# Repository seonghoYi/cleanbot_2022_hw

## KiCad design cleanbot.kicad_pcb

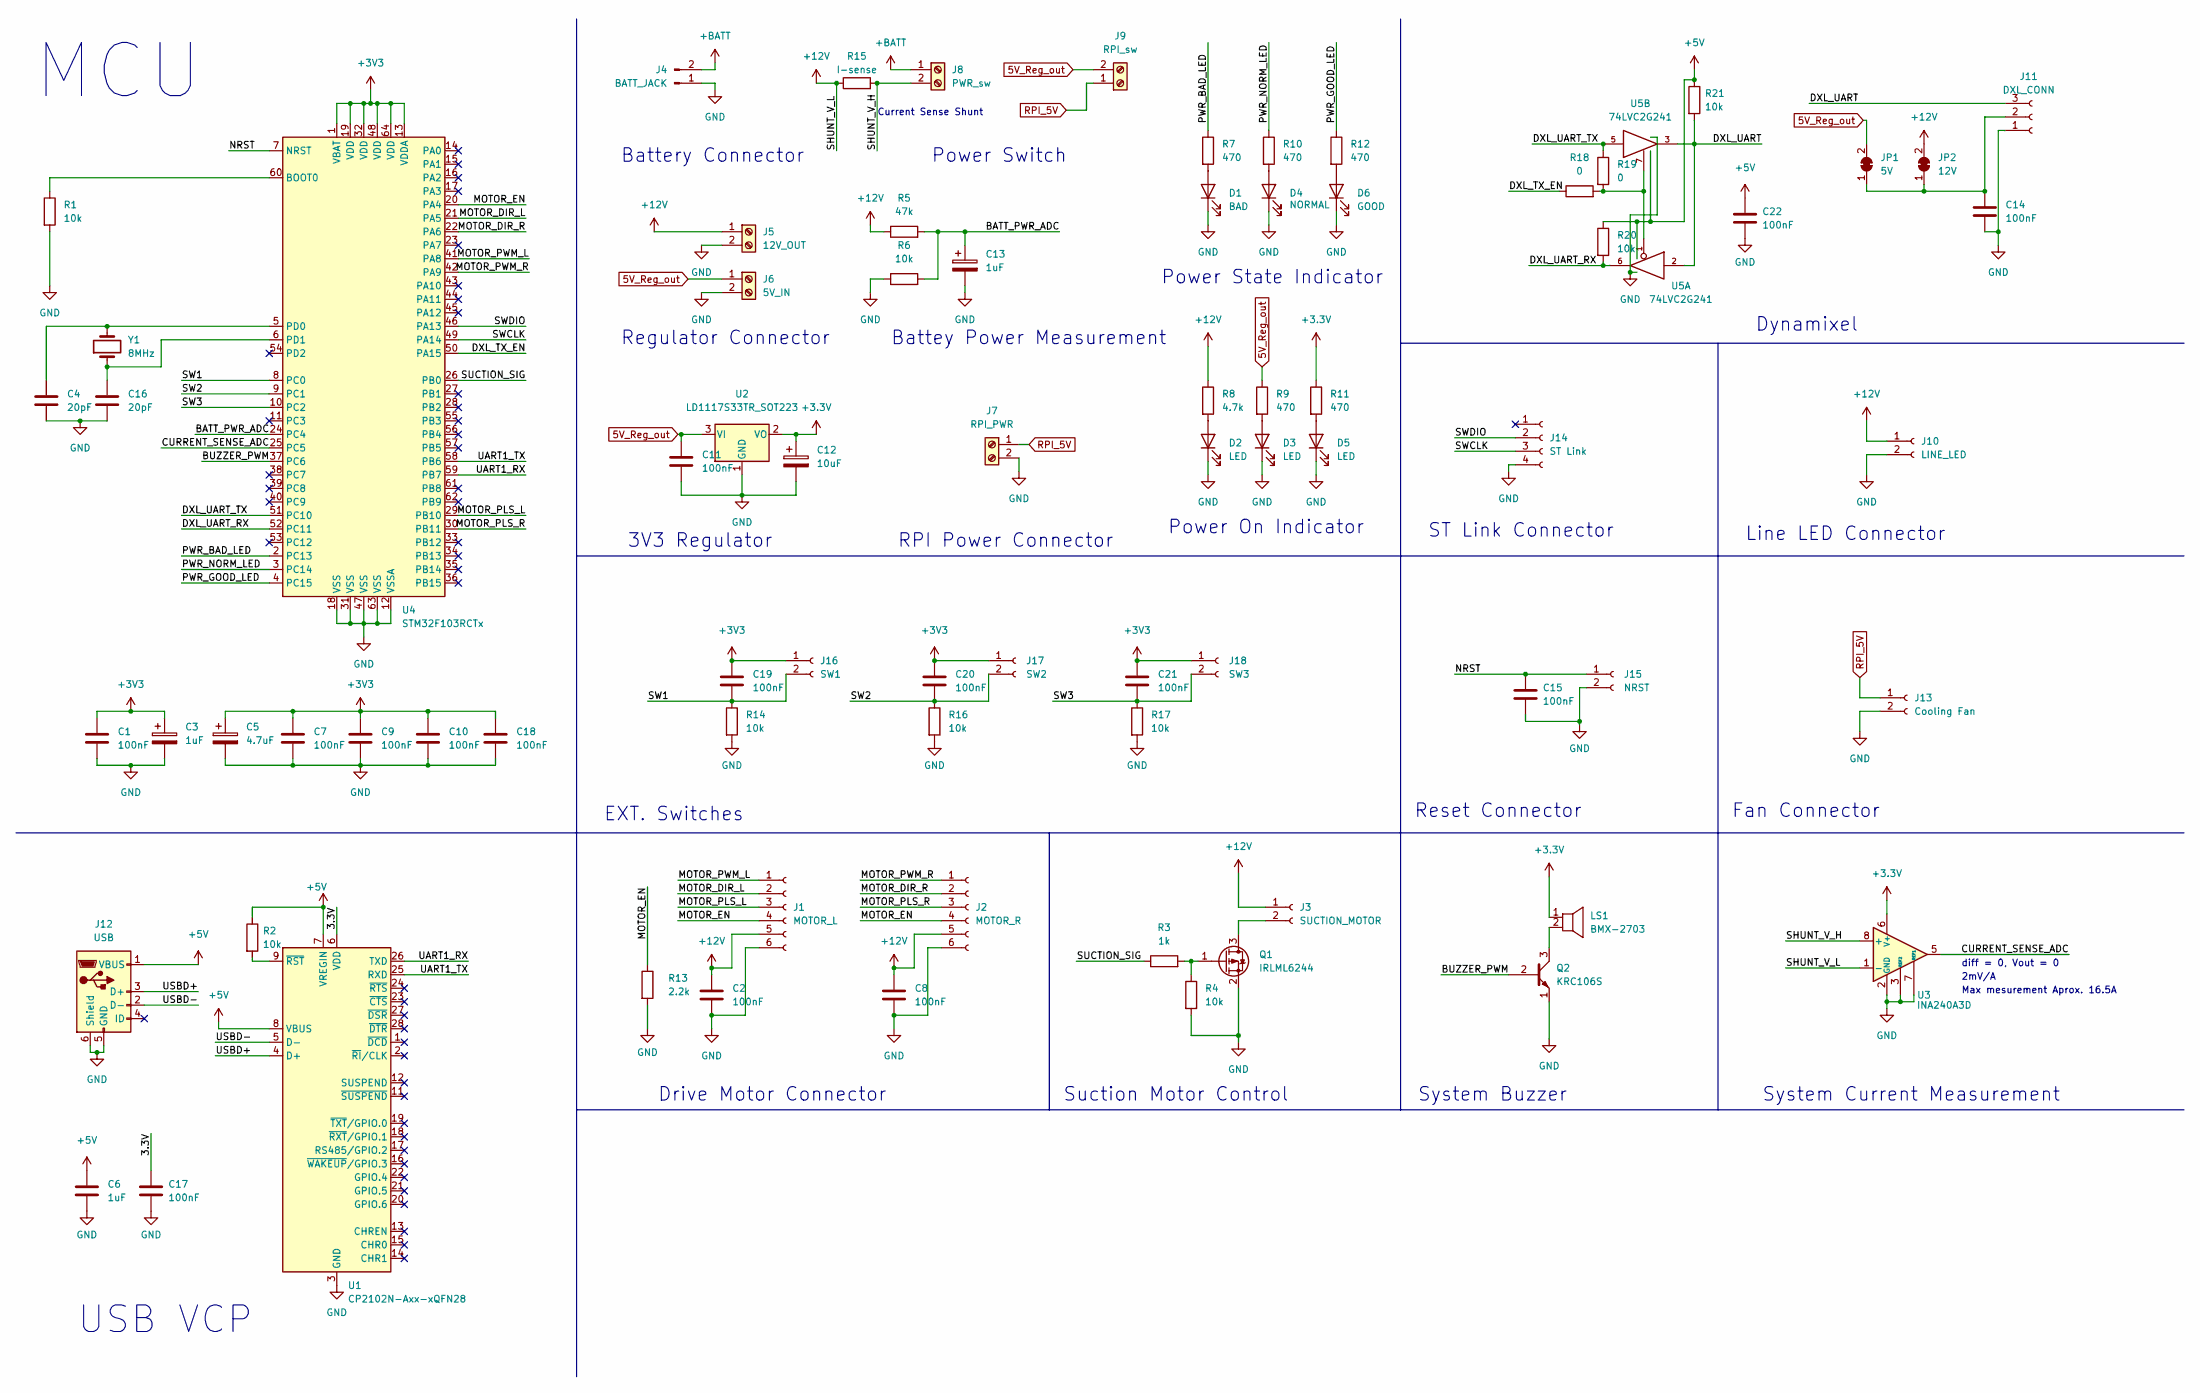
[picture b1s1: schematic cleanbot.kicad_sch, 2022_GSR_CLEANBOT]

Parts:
C1, C2, C7, C8, C9, C10, C11, C14, C15, C17, C18, C19, C20, C21, C22: 100nF; C_0603_1608Metric_Pad1.08x0.95mm_HandSolder
C3, C13: 1uF; CP_EIA-3216-18_Kemet-A
C4, C16: 20pF; C_0603_1608Metric_Pad1.08x0.95mm_HandSolder
C5: 4.7uF; CP_EIA-3216-18_Kemet-A
C6: 1uF; C_0603_1608Metric_Pad1.08x0.95mm_HandSolder
C12: 10uF; CP_EIA-3216-18_Kemet-A
D1: BAD; LED_0603_1608Metric_Pad1.05x0.95mm_HandSolder
D2, D3, D5: LED; LED_0603_1608Metric_Pad1.05x0.95mm_HandSolder
D4: NORMAL; LED_0603_1608Metric_Pad1.05x0.95mm_HandSolder
D6: GOOD; LED_0603_1608Metric_Pad1.05x0.95mm_HandSolder
J1: MOTOR_L; Molex_SPOX_5267-06A_1x06_P2.50mm_Vertical
J2: MOTOR_R; Molex_SPOX_5267-06A_1x06_P2.50mm_Vertical
J3: SUCTION_MOTOR; Molex_SPOX_5267-02A_1x02_P2.50mm_Vertical
J4: BATT_JACK; AMASS_XT30U-F_1x02_P5.0mm_Vertical
J5: 12V_OUT; Molex_Mini-Fit_Jr_5566-02A_2x01_P4.20mm_Vertical
J6: 5V_IN; Molex_Mini-Fit_Jr_5566-02A_2x01_P4.20mm_Vertical
J7: RPI_PWR; Molex_Mini-Fit_Jr_5566-02A_2x01_P4.20mm_Vertical
J8: PWR_sw; Molex_Mini-Fit_Jr_5566-02A_2x01_P4.20mm_Vertical
J9: RPI_sw; Molex_Mini-Fit_Jr_5566-02A_2x01_P4.20mm_Vertical
J10: LINE_LED; Molex_SPOX_5267-02A_1x02_P2.50mm_Vertical
J11: DXL_CONN; Molex_SPOX_5267-03A_1x03_P2.50mm_Vertical
J12: USB; USB_Micro_AB_HandSoldering
J13: Cooling Fan; Molex_SPOX_5267-02A_1x02_P2.50mm_Vertical
J14: ST Link; 5045-04
J15: NRST; Molex_SPOX_5267-02A_1x02_P2.50mm_Vertical
J16: SW1; Molex_SPOX_5267-02A_1x02_P2.50mm_Vertical
J17: SW2; Molex_SPOX_5267-02A_1x02_P2.50mm_Vertical
J18: SW3; Molex_SPOX_5267-02A_1x02_P2.50mm_Vertical
JP1: 5V; SolderJumper-2_P1.3mm_Open_RoundedPad1.0x1.5mm
JP2: 12V; SolderJumper-2_P1.3mm_Open_RoundedPad1.0x1.5mm
LS1: BMX-2703
Q1: IRLML6244; SOT-23
Q2: KRC106S; SOT-23
R1, R2, R4, R6, R14, R16, R17, R20, R21: 10k; R_0603_1608Metric_Pad0.98x0.95mm_HandSolder
R3: 1k; R_0603_1608Metric_Pad0.98x0.95mm_HandSolder
R5: 47k; R_0603_1608Metric_Pad0.98x0.95mm_HandSolder
R7, R9, R10, R11, R12: 470; R_0603_1608Metric_Pad0.98x0.95mm_HandSolder
R8: 4.7k; R_0603_1608Metric_Pad0.98x0.95mm_HandSolder
R13: 2.2k; R_0603_1608Metric_Pad0.98x0.95mm_HandSolder
R15: I-sense; Shunt_6.3x3.3mm_SMD
R18, R19: 0; R_0603_1608Metric_Pad0.98x0.95mm_HandSolder
U1: CP2102N-Axx-xQFN28; QFN-28-1EP_5x5mm_P0.5mm_EP3.35x3.35mm
U2: LD1117S33TR_SOT223; SOT-223-3_TabPin2
U3: INA240A3D; SOIC-8_3.9x4.9mm_P1.27mm
U4: STM32F103RCTx; LQFP-64_10x10mm_P0.5mm
U5: 74LVC2G241; TSSOP-8_3x3mm_P0.65mm
Y1: 8MHz; ATS-SMD Crystal

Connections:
5V_Reg_out: C11.1, J6.1, J9.2, JP1.2 (B), R9.1, U2.3 (VI)
+5V: C6.1, C22.1, J12.1 (VBUS), R2.1, R20.1, R21.1, U1.7 (VREGIN), U1.8 (VBUS), U5.8 (VCC)
+12V: C2.1, C8.1, J1.5, J2.5, J3.1, J5.1, J10.1, JP2.2 (B), R5.1, R8.1, R15.1, U3.1 (-)
+BATT: J4.2, J8.1
/3.3V: C17.1, U1.6 (VDD)
/BATT_PWR_ADC: C13.1, R5.2, R6.2, U4.24 (PC4)
/BUZZER_PWM: Q2.2 (B), U4.37 (PC6)
/CURRENT_SENSE_ADC: U3.5, U4.25 (PC5)
/DXL_TX_EN: R18.1, U4.50 (PA15)
/DXL_UART: J11.3, R21.2, U5.2, U5.3
/DXL_UART_RX: R20.2, U4.52 (PC11), U5.6
/DXL_UART_TX: R19.1, U4.51 (PC10), U5.5
/MOTOR_DIR_L: J1.2, U4.21 (PA5)
/MOTOR_DIR_R: J2.2, U4.22 (PA6)
/MOTOR_EN: J1.4, J2.4, R13.1, U4.20 (PA4)
/MOTOR_PLS_L: J1.3, U4.29 (PB10)
/MOTOR_PLS_R: J2.3, U4.30 (PB11)
/MOTOR_PWM_L: J1.1, U4.41 (PA8)
/MOTOR_PWM_R: J2.1, U4.42 (PA9)
/NRST: C15.1, J15.1, U4.7 (NRST)
/PWR_BAD_LED: R7.1, U4.2 (PC13)
/PWR_GOOD_LED: R12.1, U4.4 (PC15)
/PWR_NORM_LED: R10.1, U4.3 (PC14)
/SHUNT_V_H: J8.2, R15.2, U3.8 (+)
/SUCTION_SIG: R3.1, U4.26 (PB0)
/SW1: C19.2, J16.2, R14.1, U4.8 (PC0)
/SW2: C20.2, J17.2, R16.1, U4.9 (PC1)
/SW3: C21.2, J18.2, R17.1, U4.10 (PC2)
/SWCLK: J14.3, U4.49 (PA14)
/SWDIO: J14.2, U4.46 (PA13)
/UART1_RX: U1.26 (TXD), U4.59 (PB7)
/UART1_TX: U1.25 (RXD), U4.58 (PB6)
/USBD+: J12.3 (D+), U1.4 (D+)
/USBD-: J12.2 (D-), U1.5 (D-)
GND: C1.2, C2.2, C3.2, C4.2, C5.2, C6.2, C7.2, C8.2, C9.2, C10.2, C11.2, C12.2, C13.2, C14.1, C15.2, C16.2, C17.2, C18.2, C22.2, D1.1 (K), D2.1 (K), D3.1 (K), D4.1 (K), D5.1 (K), D6.1 (K), J1.6, J2.6, J4.1, J5.2, J6.2, J7.2, J10.2, J11.1, J12.5 (GND), J12.6 (Shield), J13.2, J14.4, J15.2, Q1.2 (S), Q2.1 (E), R1.2, R4.2, R6.1, R13.2, R14.2, R16.2, R17.2, U1.3 (GND), U1.29 (GND), U2.1 (GND), U3.2 (GND), U3.3 (REF2), U3.4 (GND), U3.7 (REF1), U4.12 (VSSA), U4.18 (VSS), U4.31 (VSS), U4.47 (VSS), U4.63 (VSS), U5.4 (GND)
unnamed: C4.1, U4.5 (PD0), Y1.2
unnamed: C14.2, J11.2, JP1.1 (A), JP2.1 (A)
unnamed: C16.1, U4.6 (PD1), Y1.1
unnamed: D1.2 (A), R7.2
unnamed: D2.2 (A), R8.2
unnamed: D3.2 (A), R9.2
unnamed: D4.2 (A), R10.2
unnamed: D5.2 (A), R11.2
unnamed: D6.2 (A), R12.2
unnamed: J3.2, Q1.3 (D)
unnamed: LS1.2 (-), Q2.3 (C)
unnamed: Q1.1 (G), R3.2, R4.1
unnamed: R1.1, U4.60 (BOOT0)
unnamed: R2.2, U1.9 (~RST)
unnamed: R18.2, R19.2, U5.1, U5.7
RPI_5V: J7.1, J9.1, J13.1

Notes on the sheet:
Suction Motor Control
Max mesurement Aprox. 16.5A
Battey Power Measurement
3V3 Regulator
Battery Connector
Reset Connector
Regulator Connector
ST Link Connector
Power On Indicator
MCU
RPI Power Connector
Fan Connector
Power Switch
Current Sense Shunt
EXT. Switches
System Current Measurement
System Buzzer
2mV/A
diff = 0, Vout = 0
Power State Indicator
Drive Motor Connector
Dynamixel
Line LED Connector
USB VCP

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
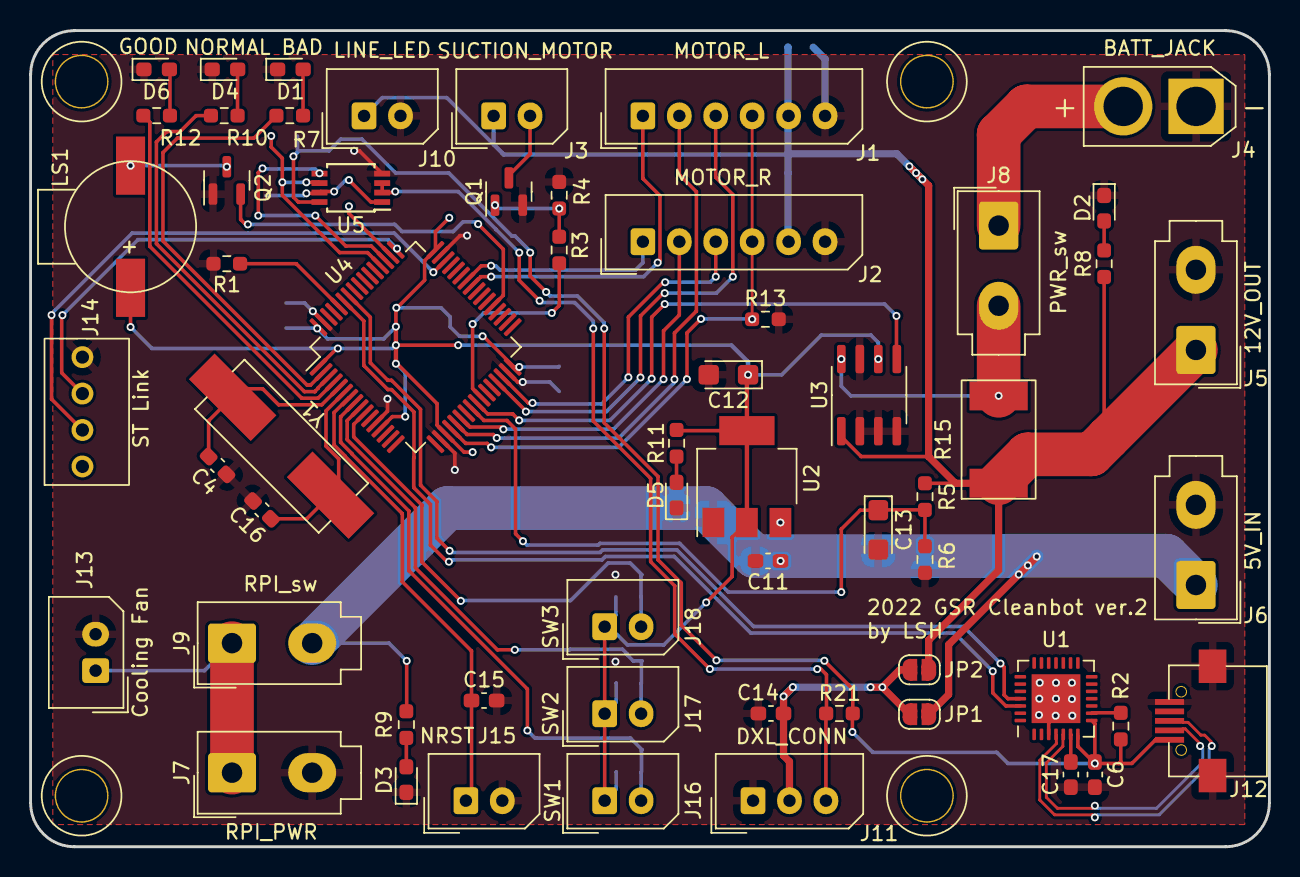
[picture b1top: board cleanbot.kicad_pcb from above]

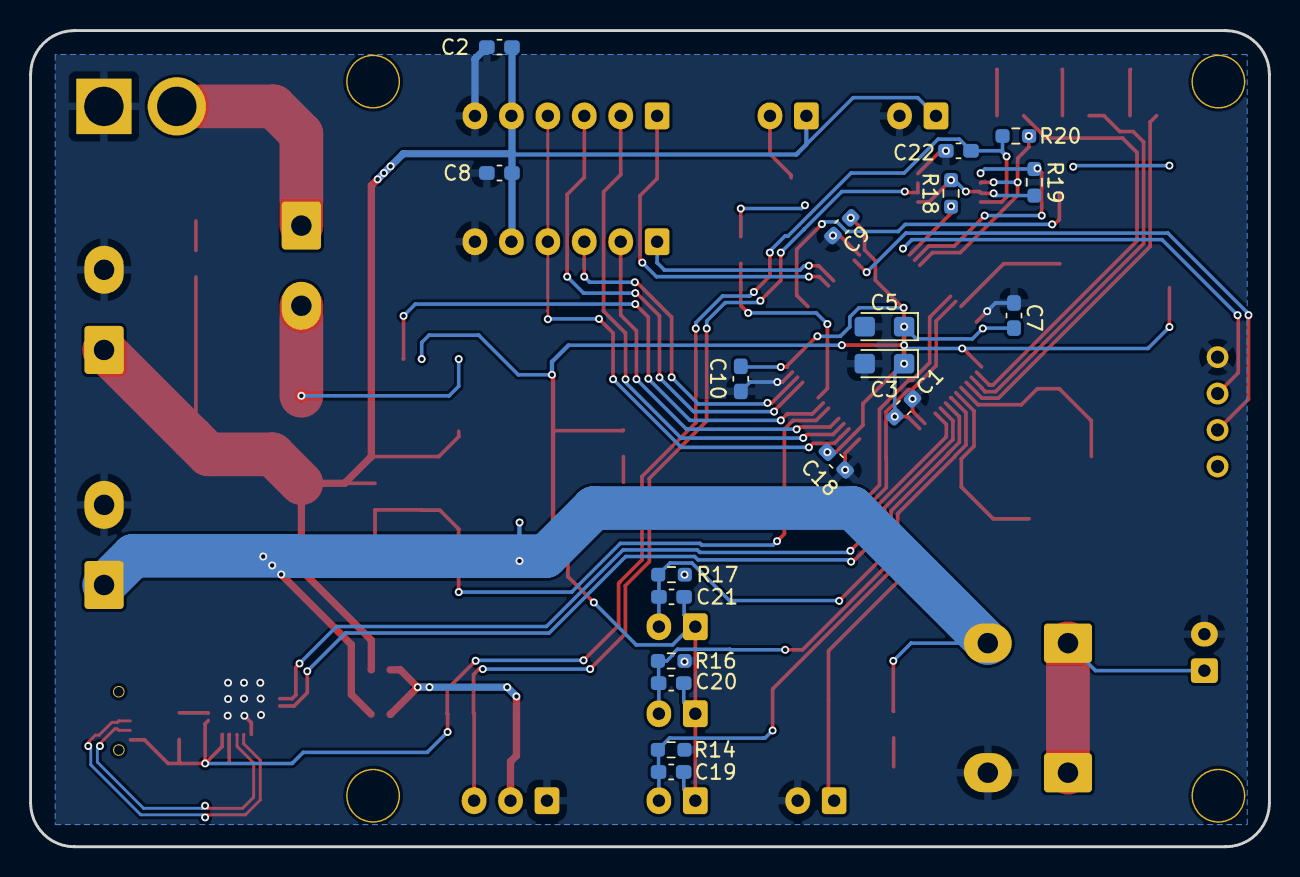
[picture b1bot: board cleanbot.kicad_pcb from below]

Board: 2 copper layers, 85.0 x 56.0 mm, 78 parts (19 on the bottom side), 52 nets.

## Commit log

2022-07-27 최초커밋
2022-08-07 두번째 버전
